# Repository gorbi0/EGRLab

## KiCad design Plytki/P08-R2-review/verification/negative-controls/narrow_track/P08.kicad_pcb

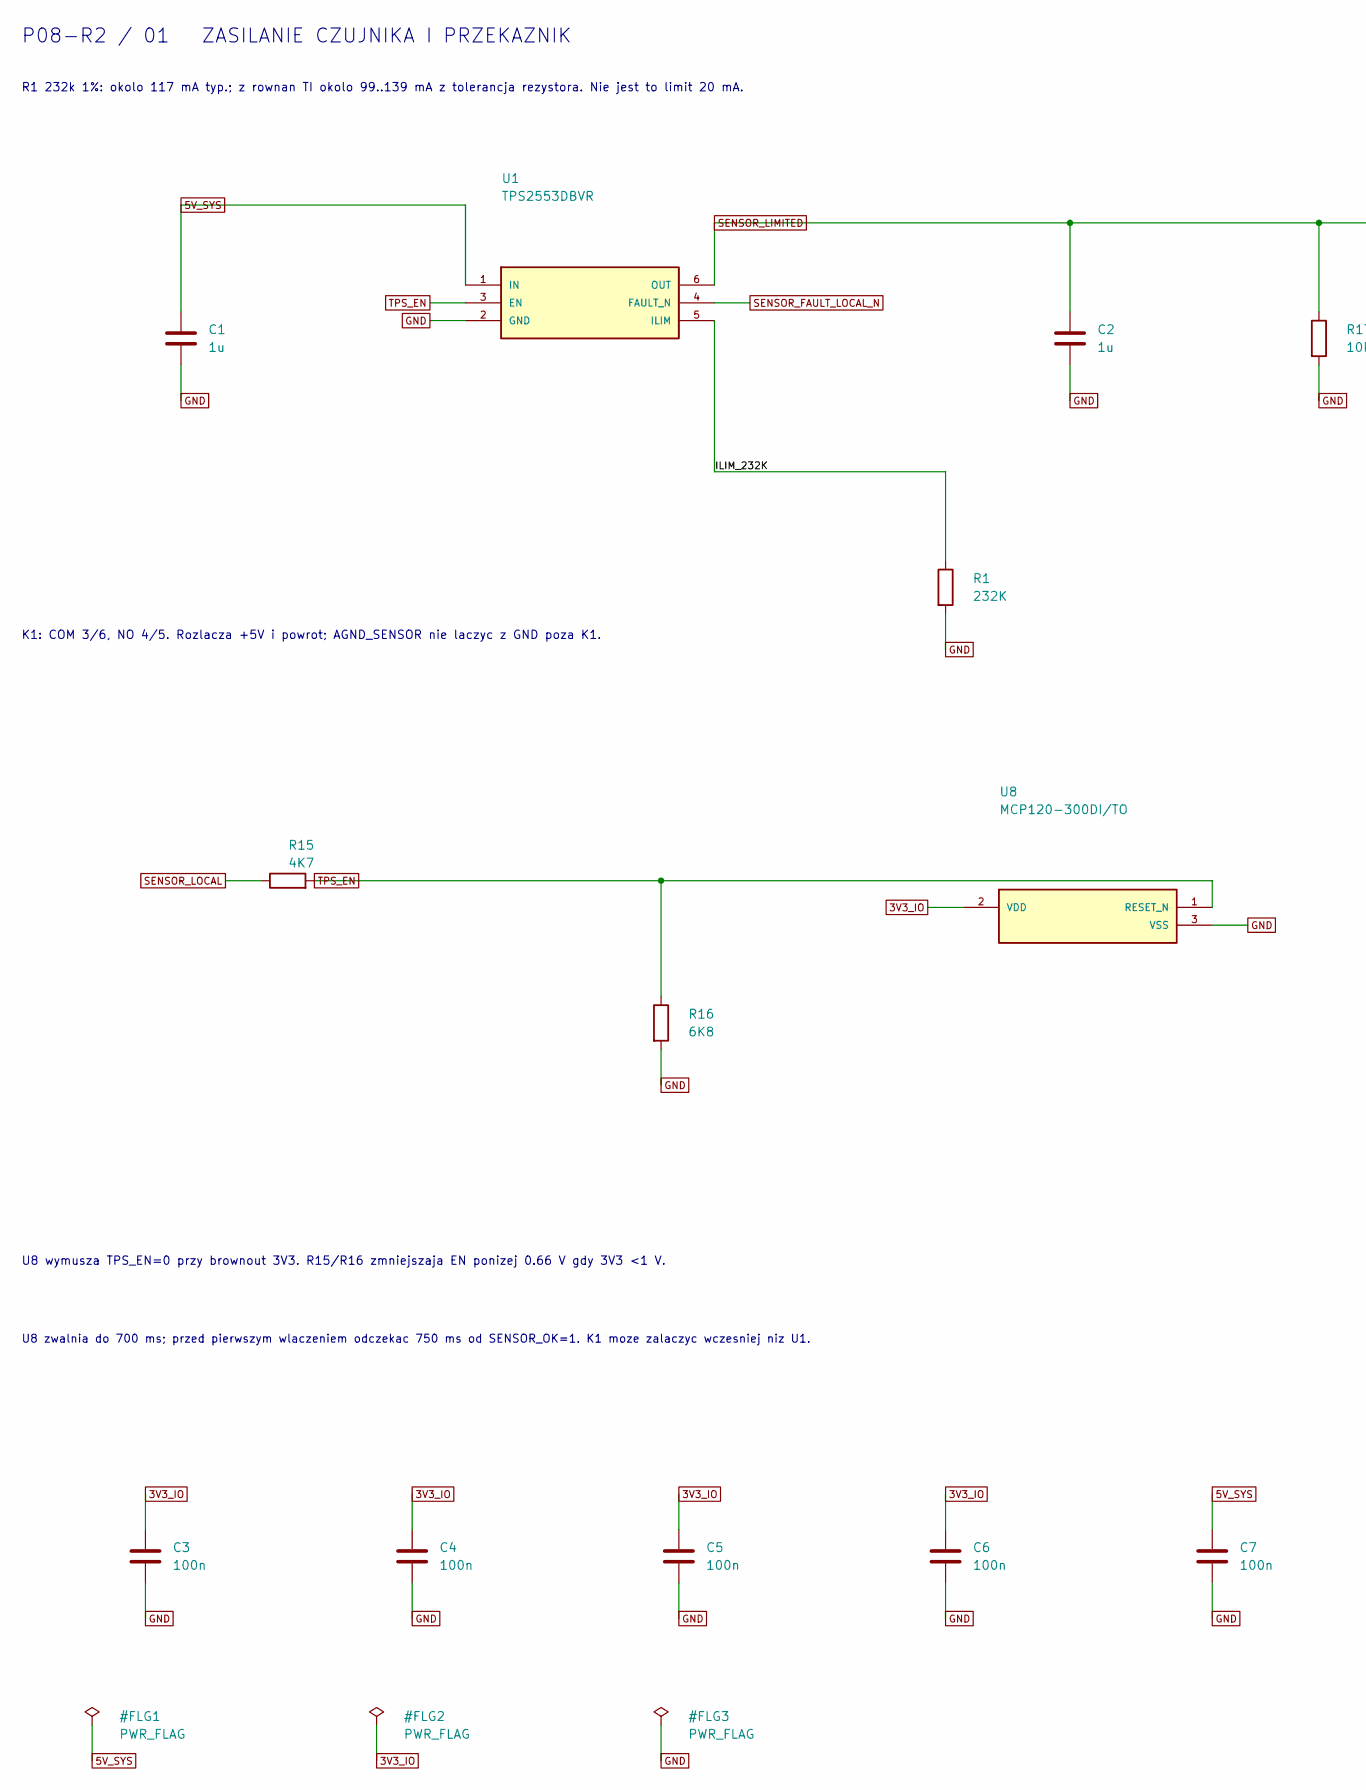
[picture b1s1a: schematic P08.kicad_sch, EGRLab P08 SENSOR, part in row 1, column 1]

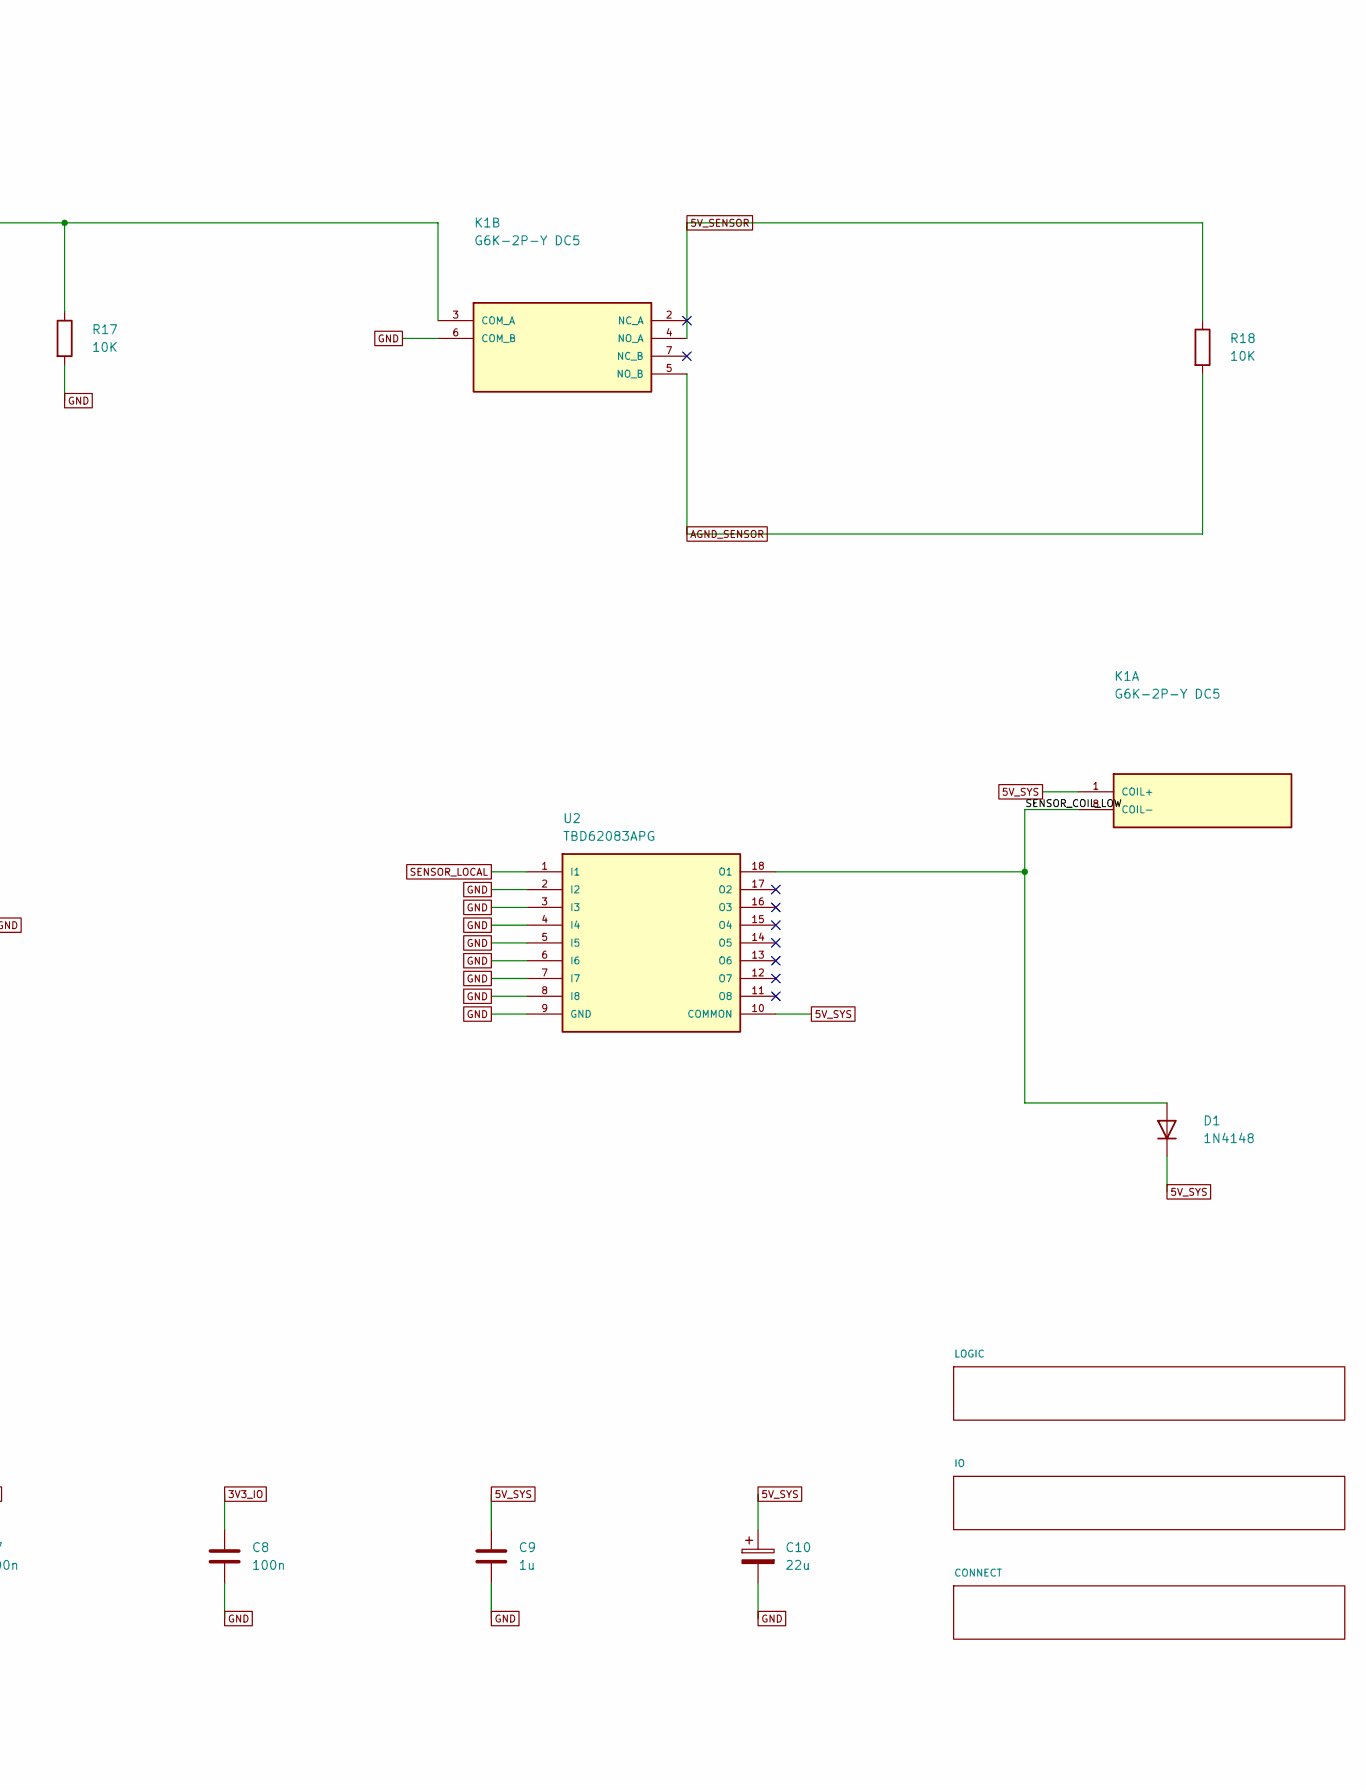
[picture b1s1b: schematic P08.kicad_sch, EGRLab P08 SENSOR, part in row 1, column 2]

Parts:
C1, C2, C9: 1u; C_1206_3216Metric_Pad1.33x1.80mm_HandSolder; MPN SMD 1206 X7R 25V 10% 1u
C3, C4, C5, C6, C7, C8: 100n; C_1206_3216Metric_Pad1.33x1.80mm_HandSolder; MPN SMD 1206 X7R 25V 10% 100n
C10: 22u; CP_Radial_D5.0mm_P2.00mm; MPN EEUFR1E220
D1: 1N4148; D_DO-35_SOD27_P7.62mm_Horizontal; MPN 1N4148
K1: G6K-2P-Y DC5; G6K_2P_Y_verified; MPN G6K-2P-Y DC5
R1: 232K; R_1206_3216Metric_Pad1.30x1.75mm_HandSolder; MPN SMD 1206 1% 0.25W 232K
R15: 4K7; R_Axial_DIN0207_L6.3mm_D2.5mm_P5.08mm_Vertical; MPN MF0207FTE-4K7 Yageo 4.7k 1% 0.6W (owned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
R16: 6K8; R_Axial_DIN0204_L3.6mm_D1.6mm_P2.54mm_Vertical; MPN MF0204FTE52-6K8 Yageo 6.8k 1% 0.4W (own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
R17, R18: 10K; R_1206_3216Metric_Pad1.30x1.75mm_HandSolder; MPN SMD 1206 1% 0.25W 10K
U1: TPS2553DBVR; SOT-23-6; MPN TPS2553DBVR
U2: TBD62083APG; DIP-18_W7.62mm; MPN TBD62083APG
U8: MCP120-300DI/TO; TO-92_Inline_Wide; MPN MCP120-300DI/TO

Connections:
3V3_IO: C3.1, C4.1, C5.1, C6.1, C8.1, U8.2 (VDD); also elsewhere on the board
5V_SENSOR: K1.4 (NO_A), R18.1; also elsewhere on the board
5V_SYS: C1.1, C7.1, C9.1, C10.1, D1.1 (K), K1.1 (COIL+), U1.1 (IN), U2.10 (COMMON); also elsewhere on the board
/ILIM_232K: R1.1, U1.5 (ILIM)
/SENSOR_COIL_LOW: D1.2 (A), K1.8 (COIL-), U2.18 (O1)
AGND_SENSOR: K1.5 (NO_B), R18.2; also elsewhere on the board
GND: C1.2, C2.2, C3.2, C4.2, C5.2, C6.2, C7.2, C8.2, C9.2, C10.2, K1.6 (COM_B), R1.2, R16.2, R17.2, U1.2 (GND), U2.2 (I2), U2.3 (I3), U2.4 (I4), U2.5 (I5), U2.6 (I6), U2.7 (I7), U2.8 (I8), U2.9 (GND), U8.3 (VSS); also elsewhere on the board
SENSOR_FAULT_LOCAL_N: U1.4 (FAULT_N); also elsewhere on the board
SENSOR_LIMITED: C2.1, K1.3 (COM_A), R17.1, U1.6 (OUT); also elsewhere on the board
SENSOR_LOCAL: R15.1, U2.1 (I1); also elsewhere on the board
TPS_EN: R15.2, R16.1, U1.3 (EN), U8.1 (RESET_N); also elsewhere on the board

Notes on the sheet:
R1 232k 1%: okolo 117 mA typ.; z rownan TI okolo 99..139 mA z tolerancja rezystora. Nie jest to limit 20 mA.
K1: COM 3/6, NO 4/5. Rozlacza +5V i powrot; AGND_SENSOR nie laczyc z GND poza K1.
U8 wymusza TPS_EN=0 przy brownout 3V3. R15/R16 zmniejszaja EN ponizej 0.66 V gdy 3V3 <1 V.
U8 zwalnia do 700 ms; przed pierwszym wlaczeniem odczekac 750 ms od SENSOR_OK=1. K1 moze zalaczyc wczesniej niz U1.
P08-R2 / 01 ZASILANIE CZUJNIKA I PRZEKAZNIK

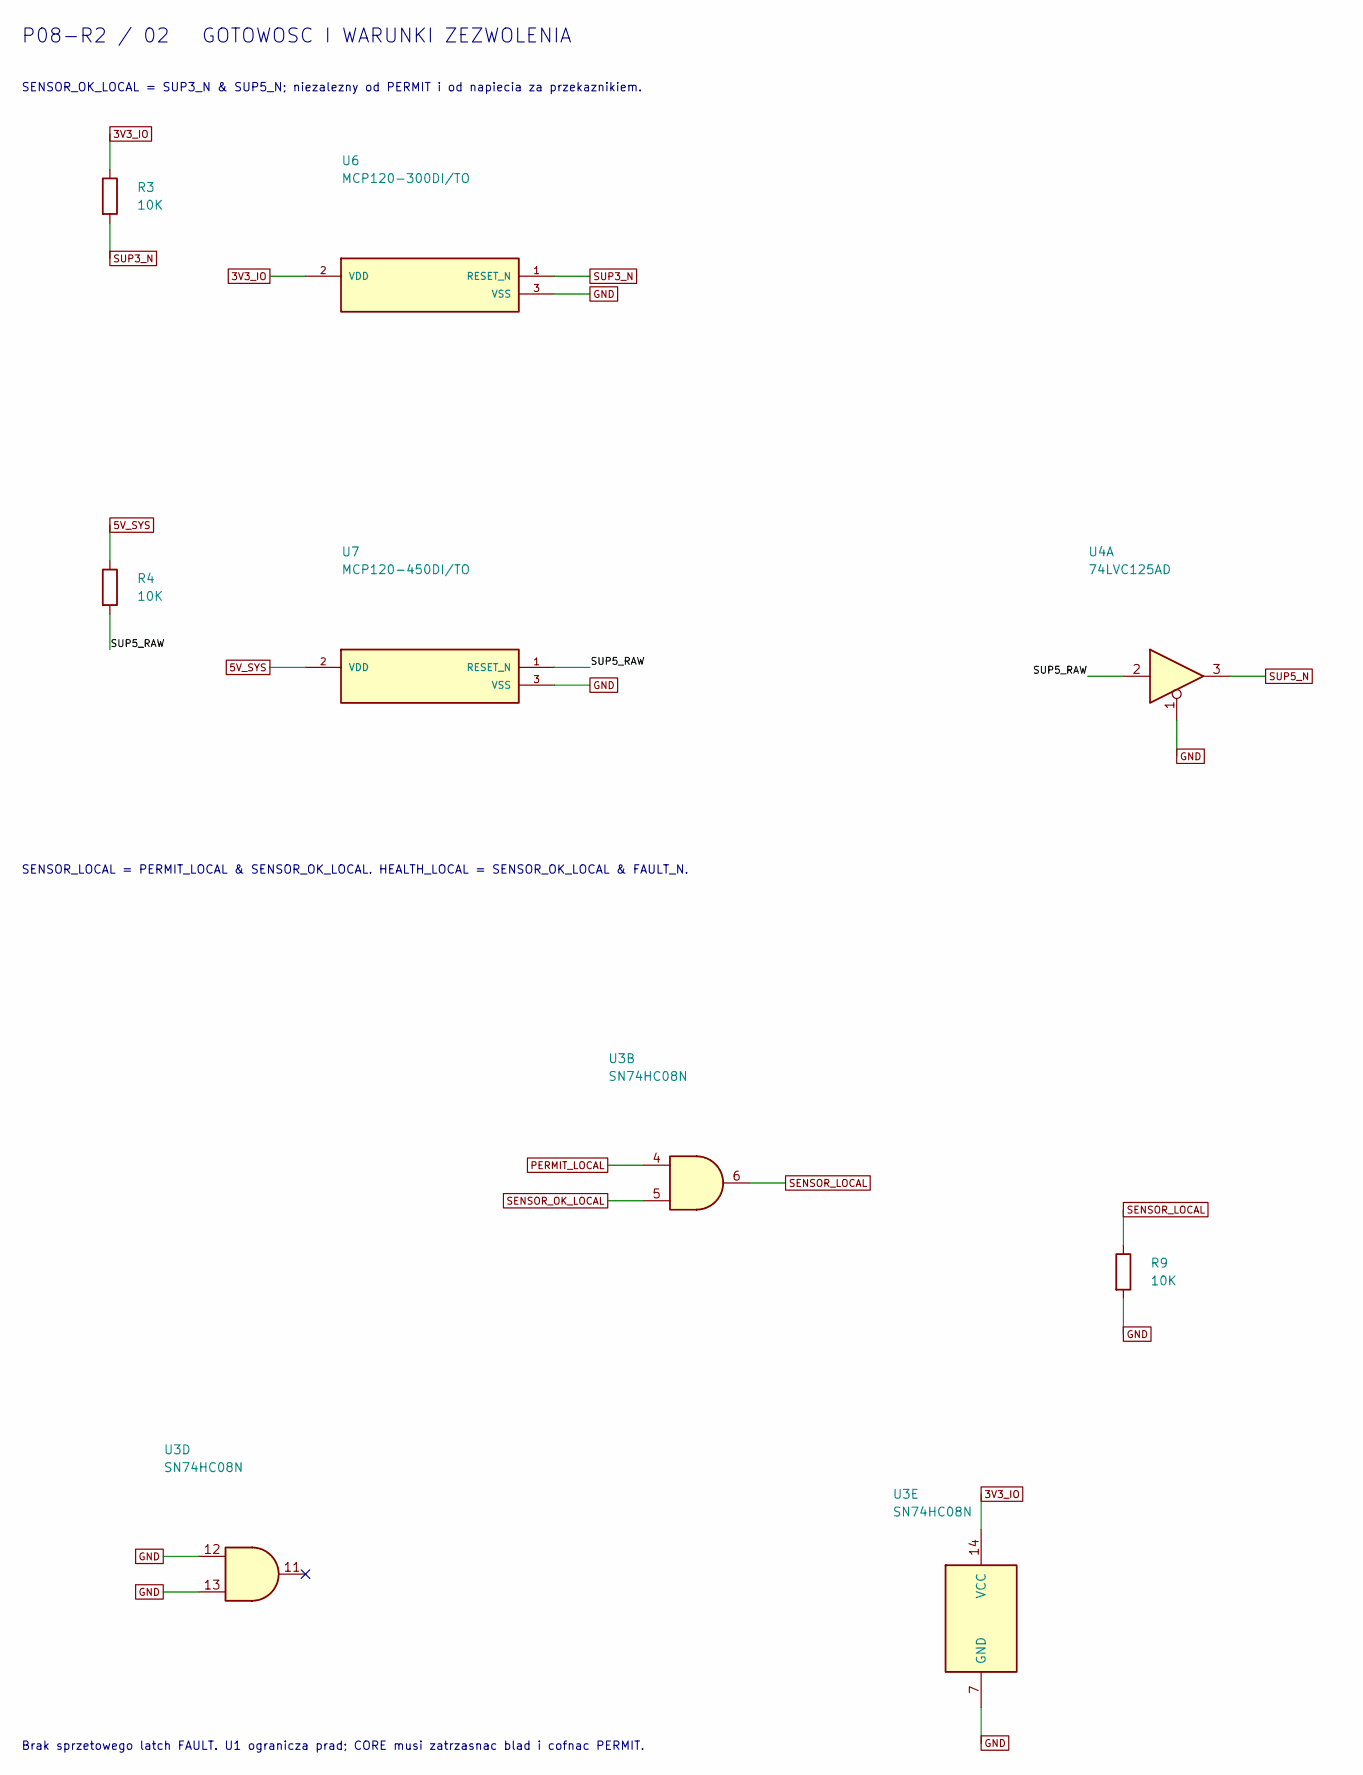
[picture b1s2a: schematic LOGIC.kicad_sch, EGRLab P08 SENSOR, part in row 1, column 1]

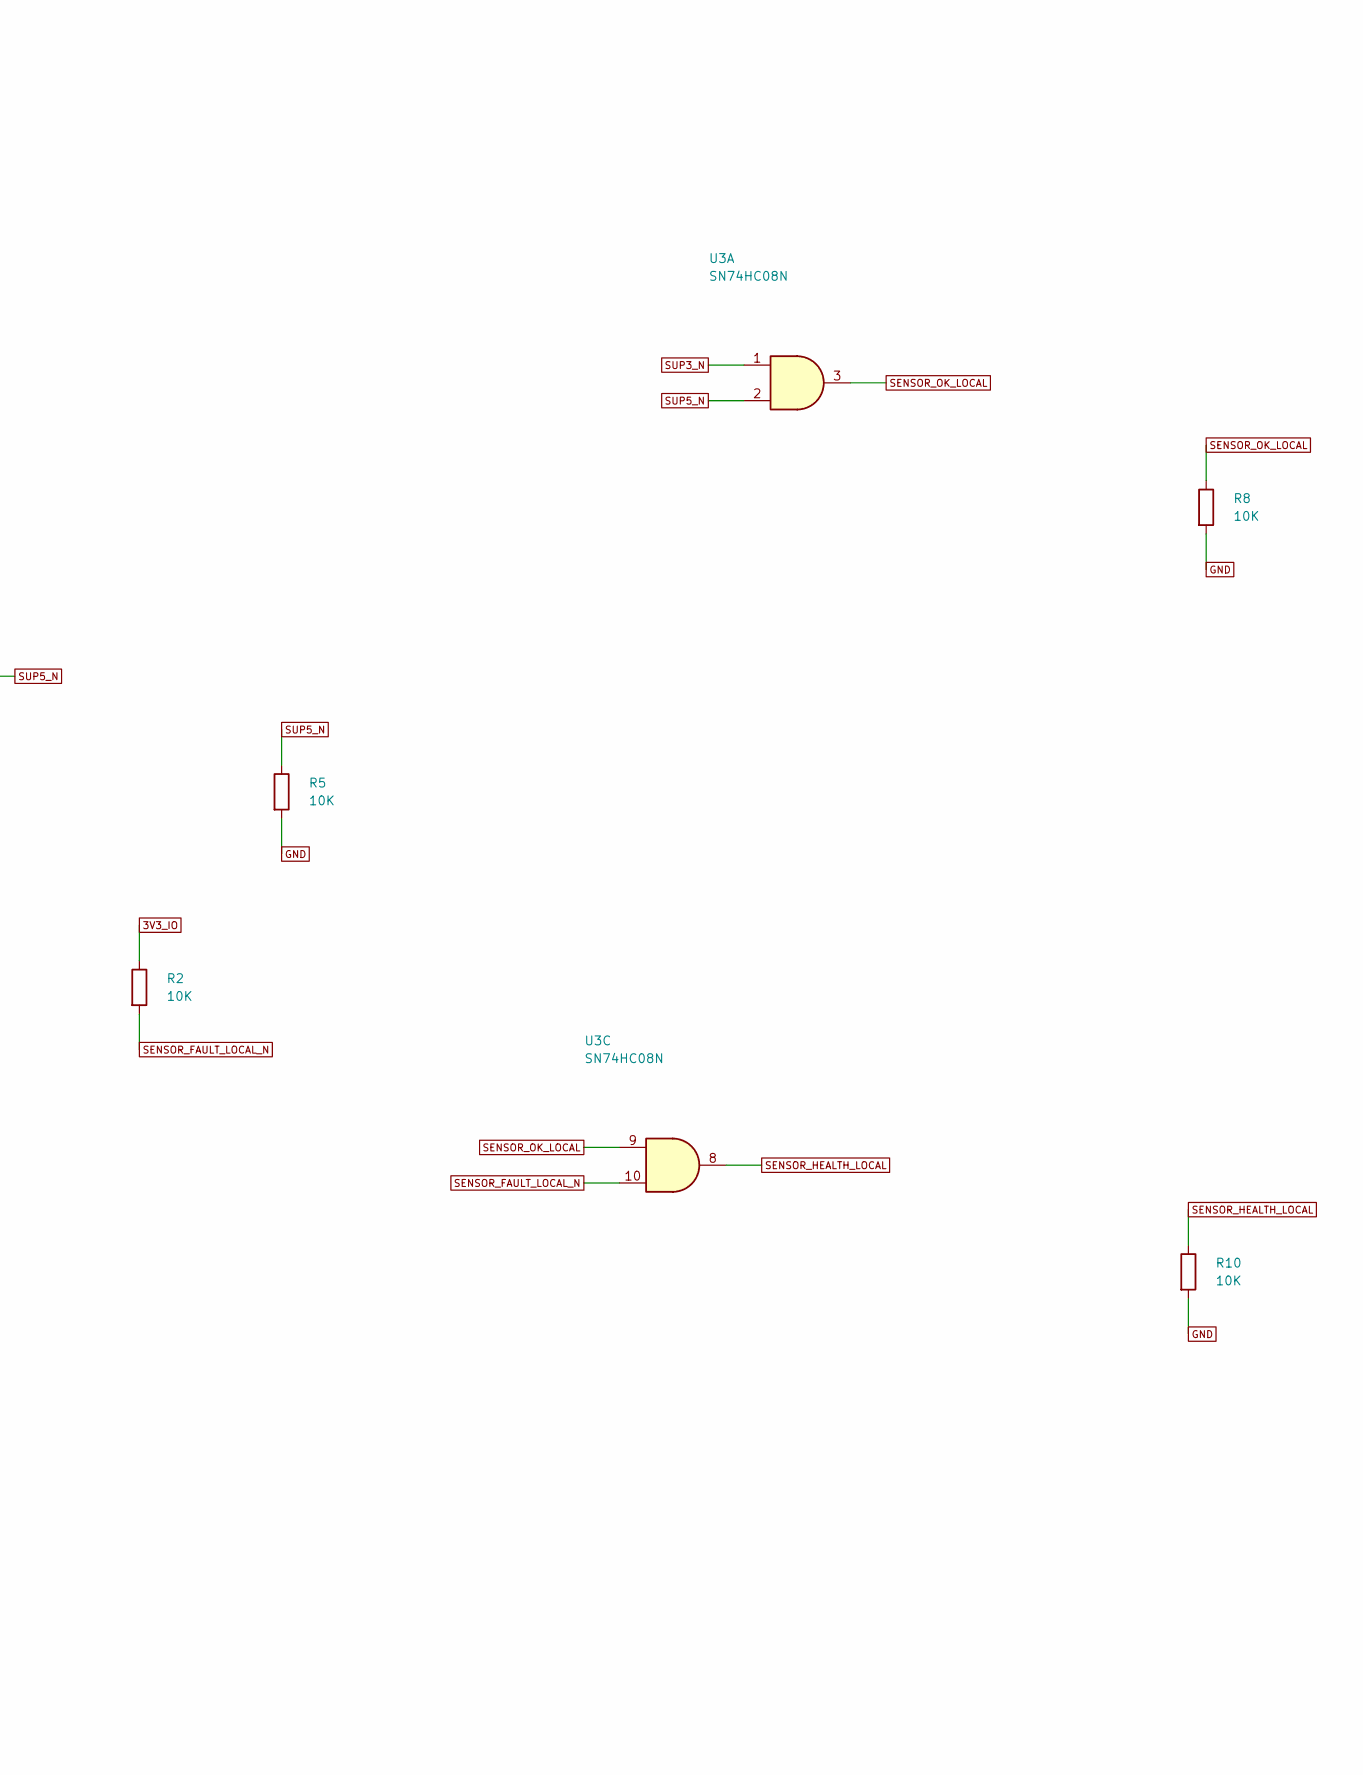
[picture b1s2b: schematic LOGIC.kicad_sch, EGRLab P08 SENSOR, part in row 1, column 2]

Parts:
R2, R3, R4, R5, R8, R9, R10: 10K; R_1206_3216Metric_Pad1.30x1.75mm_HandSolder; MPN SMD 1206 1% 0.25W 10K
U3: SN74HC08N; DIP-14_W7.62mm; MPN SN74HC08N
U4: 74LVC125AD; SOIC-14_3.9x8.7mm_P1.27mm; MPN 74LVC125AD,118 (Nexperia)
U6: MCP120-300DI/TO; TO-92_Inline_Wide; MPN MCP120-300DI/TO
U7: MCP120-450DI/TO; TO-92_Inline_Wide; MPN MCP120-450DI/TO

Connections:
3V3_IO: R2.1, R3.1, U3.14 (VCC), U6.2 (VDD); also elsewhere on the board
5V_SYS: R4.1, U7.2 (VDD); also elsewhere on the board
/LOGIC/SUP5_RAW: R4.2, U4.2, U7.1 (RESET_N)
GND: R5.2, R8.2, R9.2, R10.2, U3.7 (GND), U3.12, U3.13, U4.1, U6.3 (VSS), U7.3 (VSS); also elsewhere on the board
PERMIT_LOCAL: U3.4; also elsewhere on the board
SENSOR_FAULT_LOCAL_N: R2.2, U3.10; also elsewhere on the board
SENSOR_HEALTH_LOCAL: R10.1, U3.8; also elsewhere on the board
SENSOR_LOCAL: R9.1, U3.6; also elsewhere on the board
SENSOR_OK_LOCAL: R8.1, U3.3, U3.5, U3.9; also elsewhere on the board
SUP3_N: R3.2, U3.1, U6.1 (RESET_N); also elsewhere on the board
SUP5_N: R5.1, U3.2, U4.3; also elsewhere on the board

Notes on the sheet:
SENSOR_OK_LOCAL = SUP3_N & SUP5_N; niezalezny od PERMIT i od napiecia za przekaznikiem.
SENSOR_LOCAL = PERMIT_LOCAL & SENSOR_OK_LOCAL. HEALTH_LOCAL = SENSOR_OK_LOCAL & FAULT_N.
Brak sprzetowego latch FAULT. U1 ogranicza prad; CORE musi zatrzasnac blad i cofnac PERMIT.
P08-R2 / 02 GOTOWOSC I WARUNKI ZEZWOLENIA

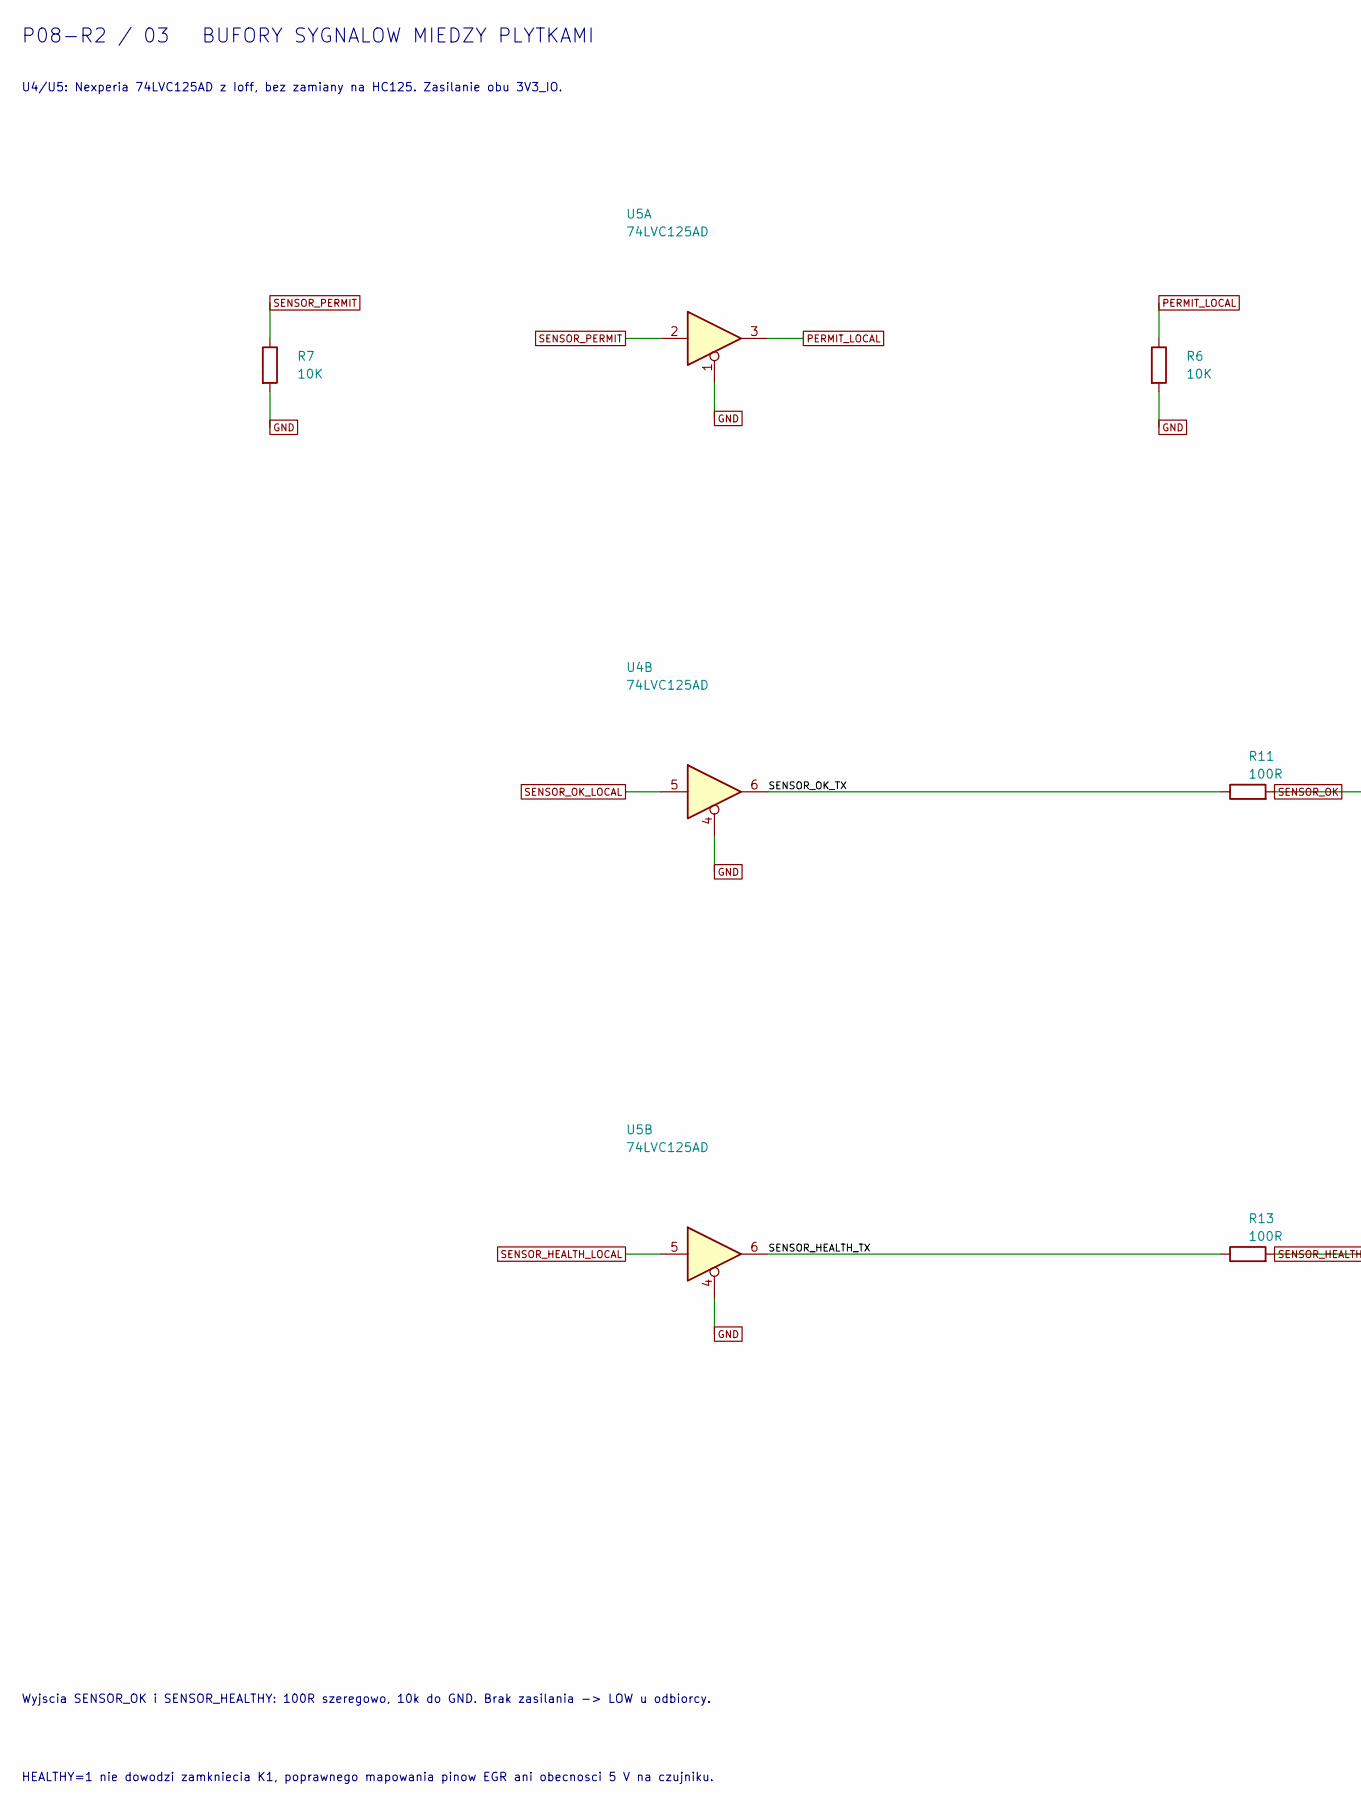
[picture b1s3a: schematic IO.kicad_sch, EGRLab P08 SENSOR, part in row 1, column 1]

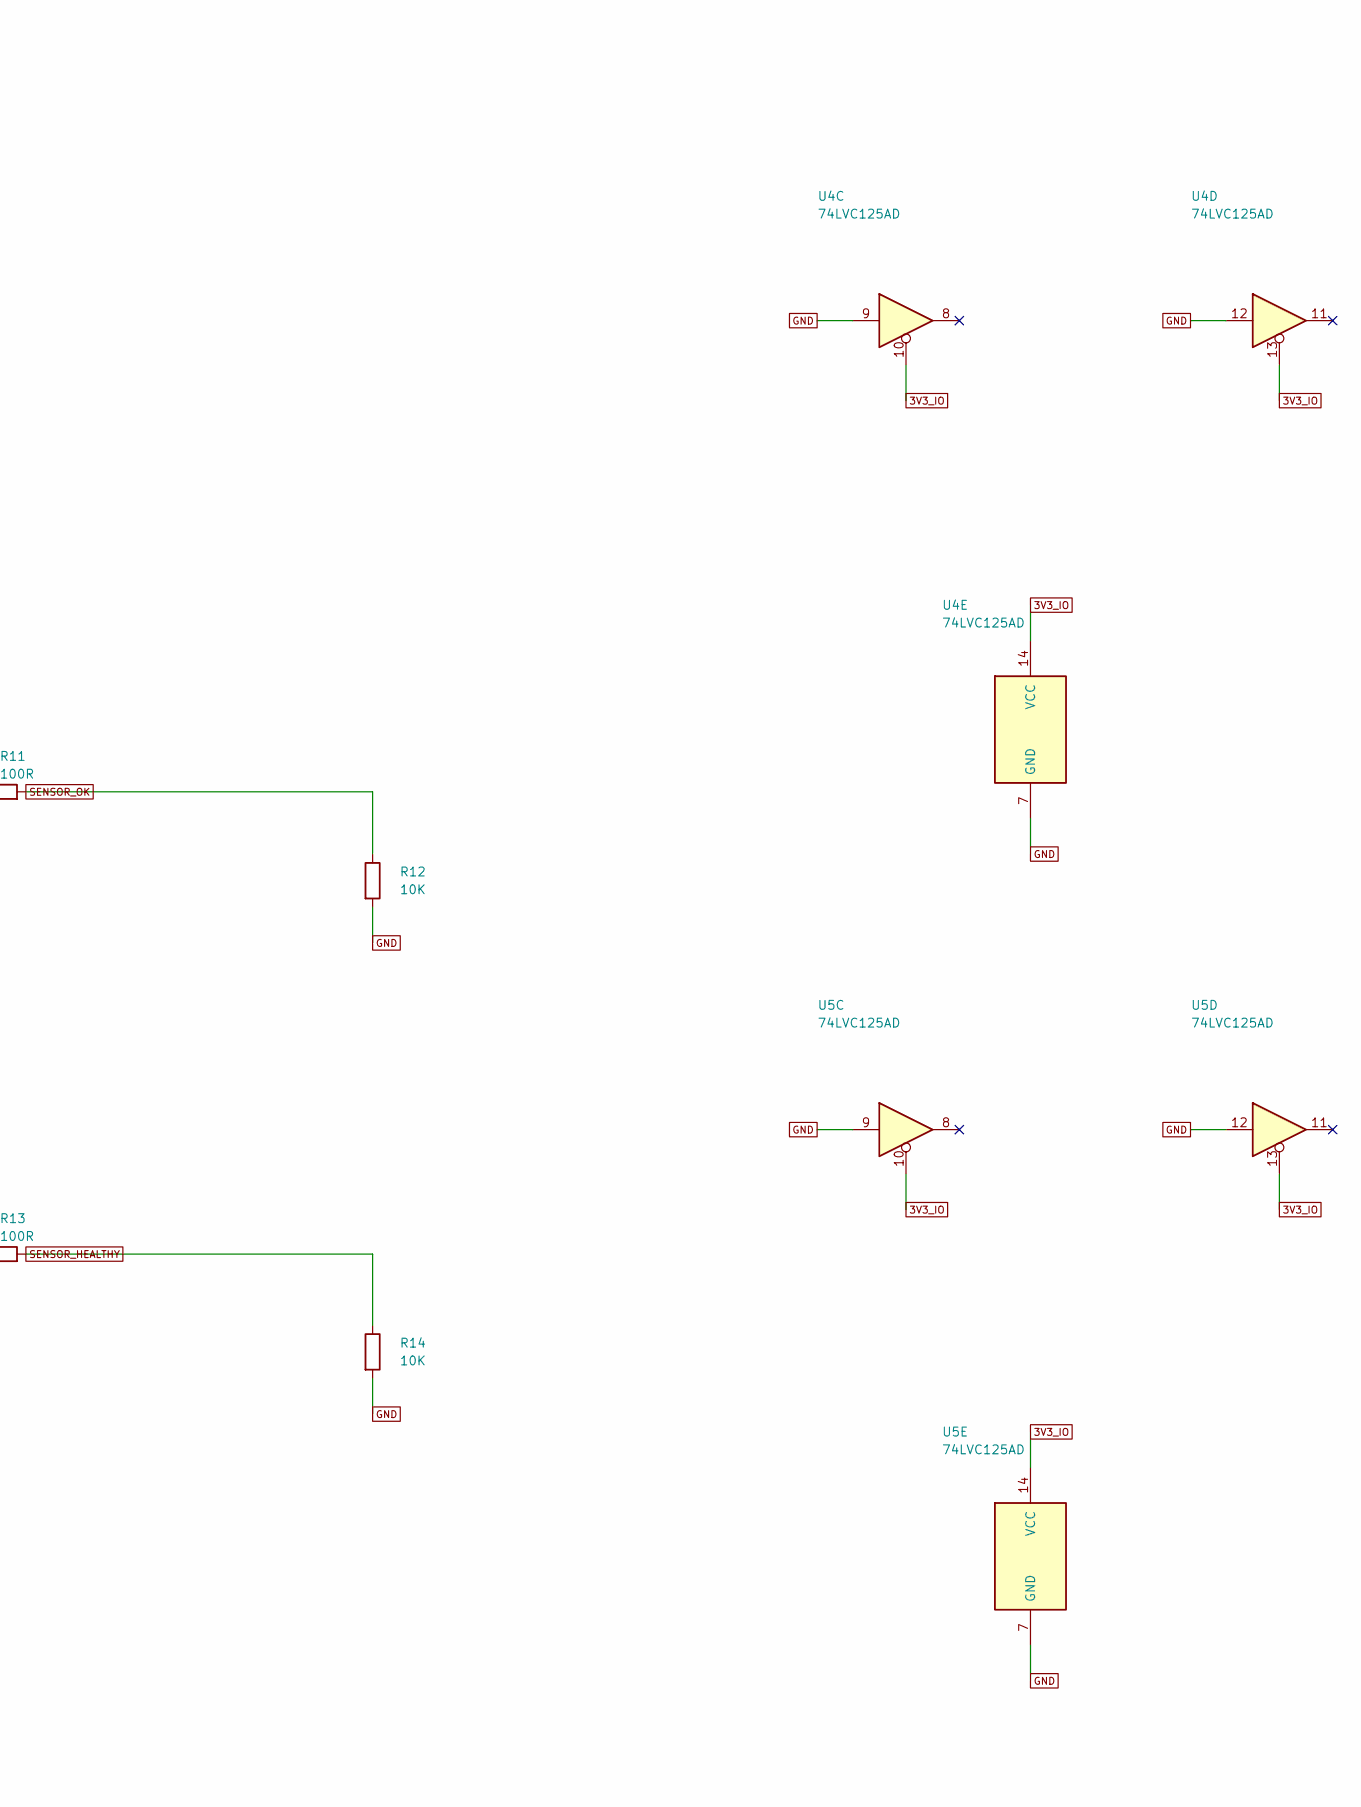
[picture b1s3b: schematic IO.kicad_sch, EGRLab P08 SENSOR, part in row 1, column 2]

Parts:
R6, R7, R12, R14: 10K; R_1206_3216Metric_Pad1.30x1.75mm_HandSolder; MPN SMD 1206 1% 0.25W 10K
R11, R13: 100R; R_1206_3216Metric_Pad1.30x1.75mm_HandSolder; MPN SMD 1206 1% 0.25W 100R
U4, U5: 74LVC125AD; SOIC-14_3.9x8.7mm_P1.27mm; MPN 74LVC125AD,118 (Nexperia)

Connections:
3V3_IO: U4.10, U4.13, U4.14 (VCC), U5.10, U5.13, U5.14 (VCC); also elsewhere on the board
/IO/SENSOR_HEALTH_TX: R13.1, U5.6
/IO/SENSOR_OK_TX: R11.1, U4.6
GND: R6.2, R7.2, R12.2, R14.2, U4.4, U4.7 (GND), U4.9, U4.12, U5.1, U5.4, U5.7 (GND), U5.9, U5.12; also elsewhere on the board
PERMIT_LOCAL: R6.1, U5.3; also elsewhere on the board
SENSOR_HEALTHY: R13.2, R14.1; also elsewhere on the board
SENSOR_HEALTH_LOCAL: U5.5; also elsewhere on the board
SENSOR_OK: R11.2, R12.1; also elsewhere on the board
SENSOR_OK_LOCAL: U4.5; also elsewhere on the board
SENSOR_PERMIT: R7.1, U5.2; also elsewhere on the board

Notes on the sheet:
U4/U5: Nexperia 74LVC125AD z Ioff, bez zamiany na HC125. Zasilanie obu 3V3_IO.
Wyjscia SENSOR_OK i SENSOR_HEALTHY: 100R szeregowo, 10k do GND. Brak zasilania -> LOW u odbiorcy.
HEALTHY=1 nie dowodzi zamkniecia K1, poprawnego mapowania pinow EGR ani obecnosci 5 V na czujniku.
P08-R2 / 03 BUFORY SYGNALOW MIEDZY PLYTKAMI
